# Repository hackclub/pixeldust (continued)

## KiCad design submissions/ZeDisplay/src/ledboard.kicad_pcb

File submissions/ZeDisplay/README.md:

---
name: "Burger King"
slack_id: "U07HJAL0P9Q"
tutorial: # Link to the tutorial if you used one, including the default guide
wokwi: # Link to the Wokwi project
---

# ZeDisplay

<!-- Uncomment the line below if you need a soldering iron -->
<!-- ⚠️ I would like to [reason for iron], so I would need a soldering iron. -->

A dual neopixel display with 5050 RGB LEDs and SMD-4P,2x1.8mm RGB LEDs for elegant viewing. The display is powered by a XIAO ESP32-S3 microcontroller, and uses micropython. The display is designed to be used as a decorative element in a room or as a fun project for electronics enthusiasts :)

A simplified BOM table
(pls include rough pricing of any extra components you're using)

<!-- Example: -->

| Comment           | Footprint                                      | Quantity | LCSC     | Cost   |
|-------------------|------------------------------------------------|----------|----------|--------|
| 1uF               | C_1206_3216Metric_Pad1.33x1.80mm_HandSolder    | 1        | C15008   | 0.1247$|
| 1nF               | C_0402_1005Metric_Pad0.74x0.62mm_HandSolder    | 13       | C100040  | 0.0273$|
| WS2812B           | LED_WS2812B_PLCC4_5.0x5.0mm_P3.2mm             | 80       | C22461793| 1.94$  |
| WS2812B           | XINGLIGHT XL-0807RGBC-WS2812B-S                | 140      | C41413181| 3.65$  |
| XIAO ESP32-S3     | XIAO-ESP32-S3-DIP                              | 1        |          |        |

This was more hectic to design than i imagined it to be. The power delivery was problematic, I had planned of using
USB C PD but the neotiating circuit was too complex. Not thinking about it definetly helped, I just ended up using the XIAO's 
already established power from the USB C port (implicit contract, 5V3A).

some images:

> The slikscreen has designs from the XKCD comics. <3

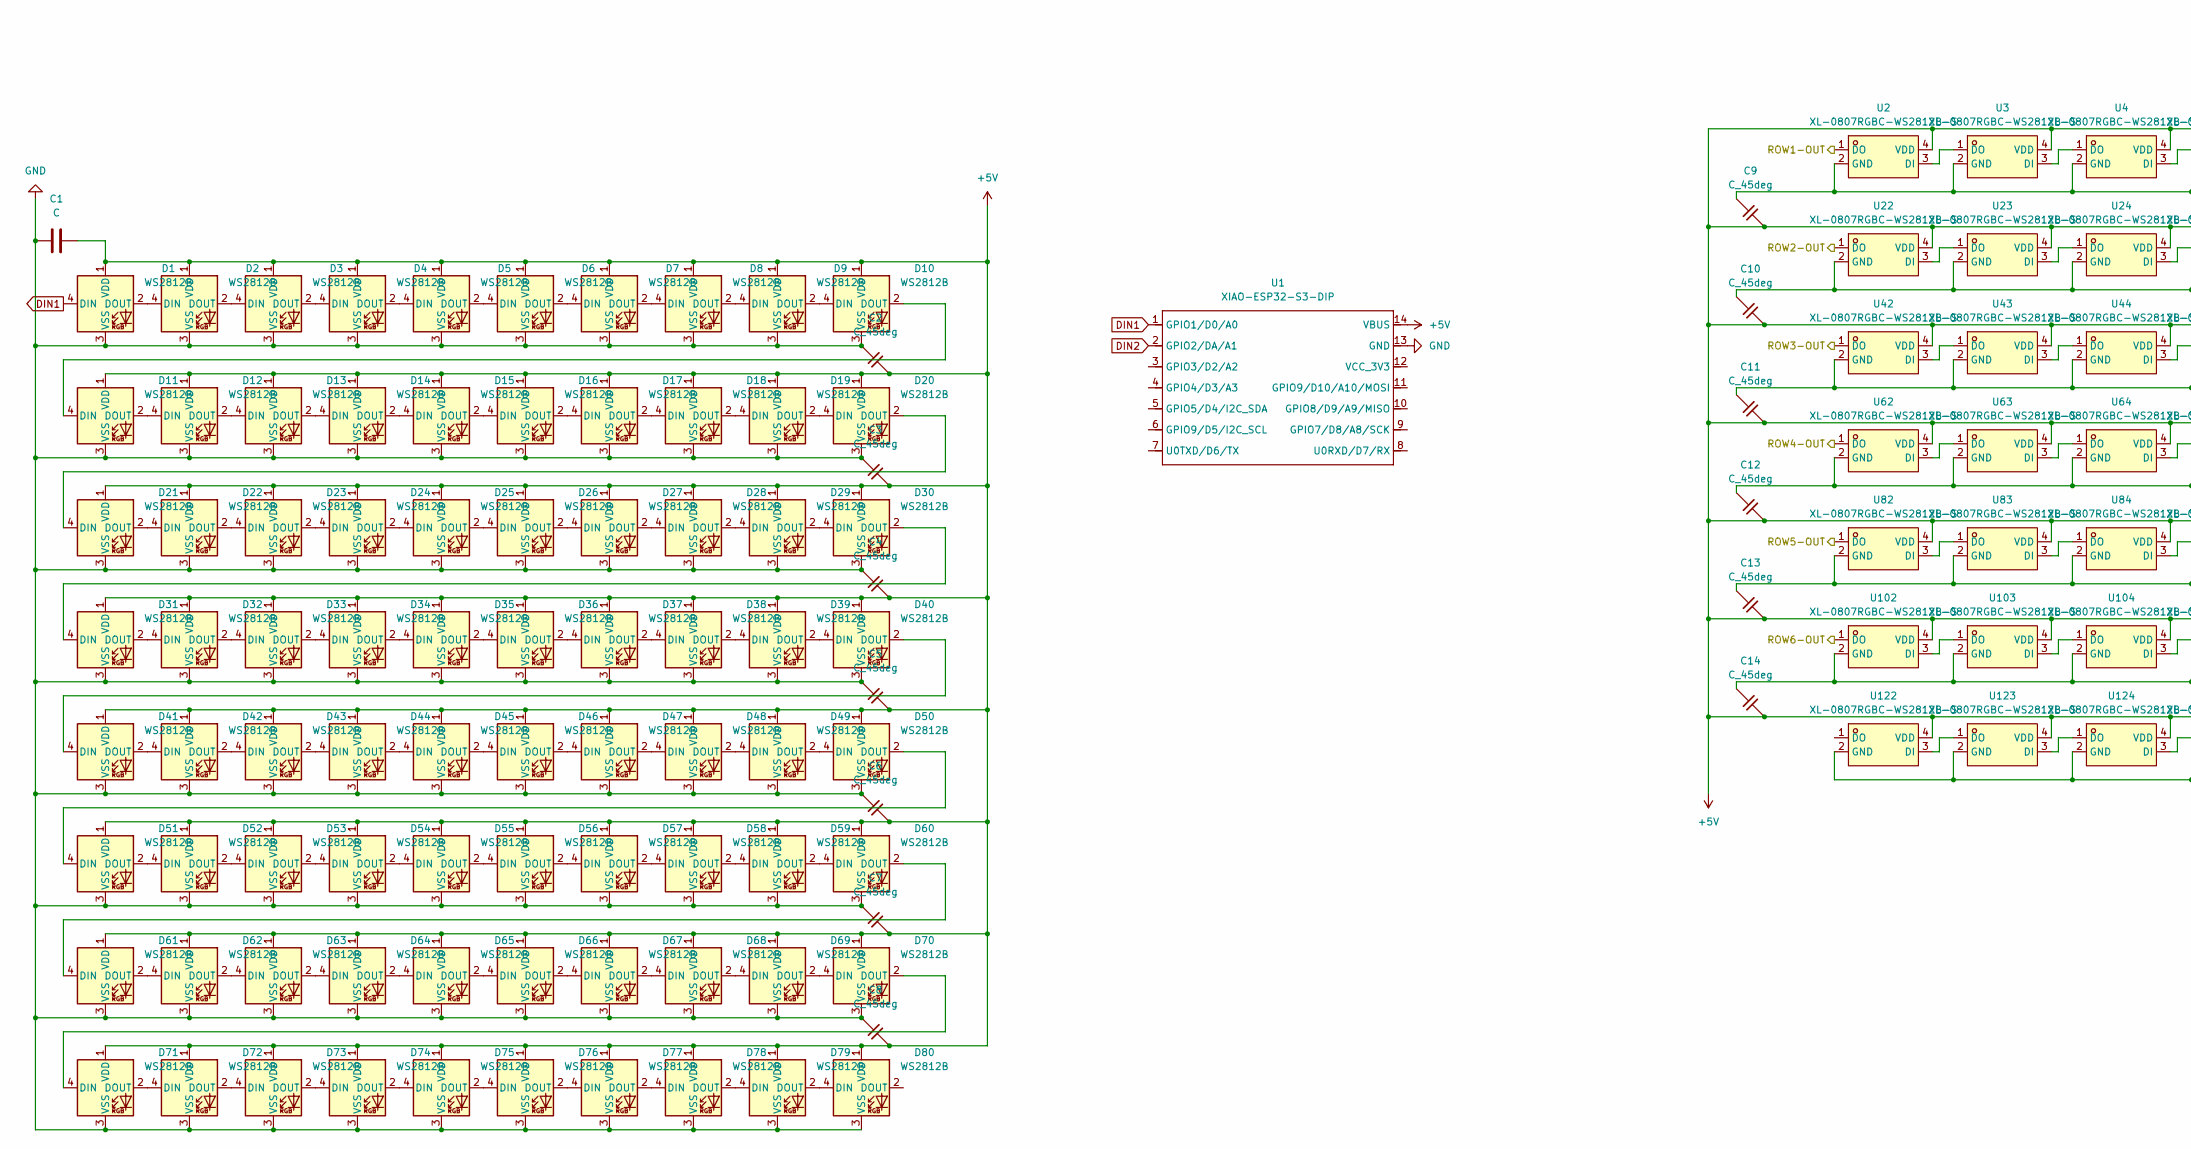
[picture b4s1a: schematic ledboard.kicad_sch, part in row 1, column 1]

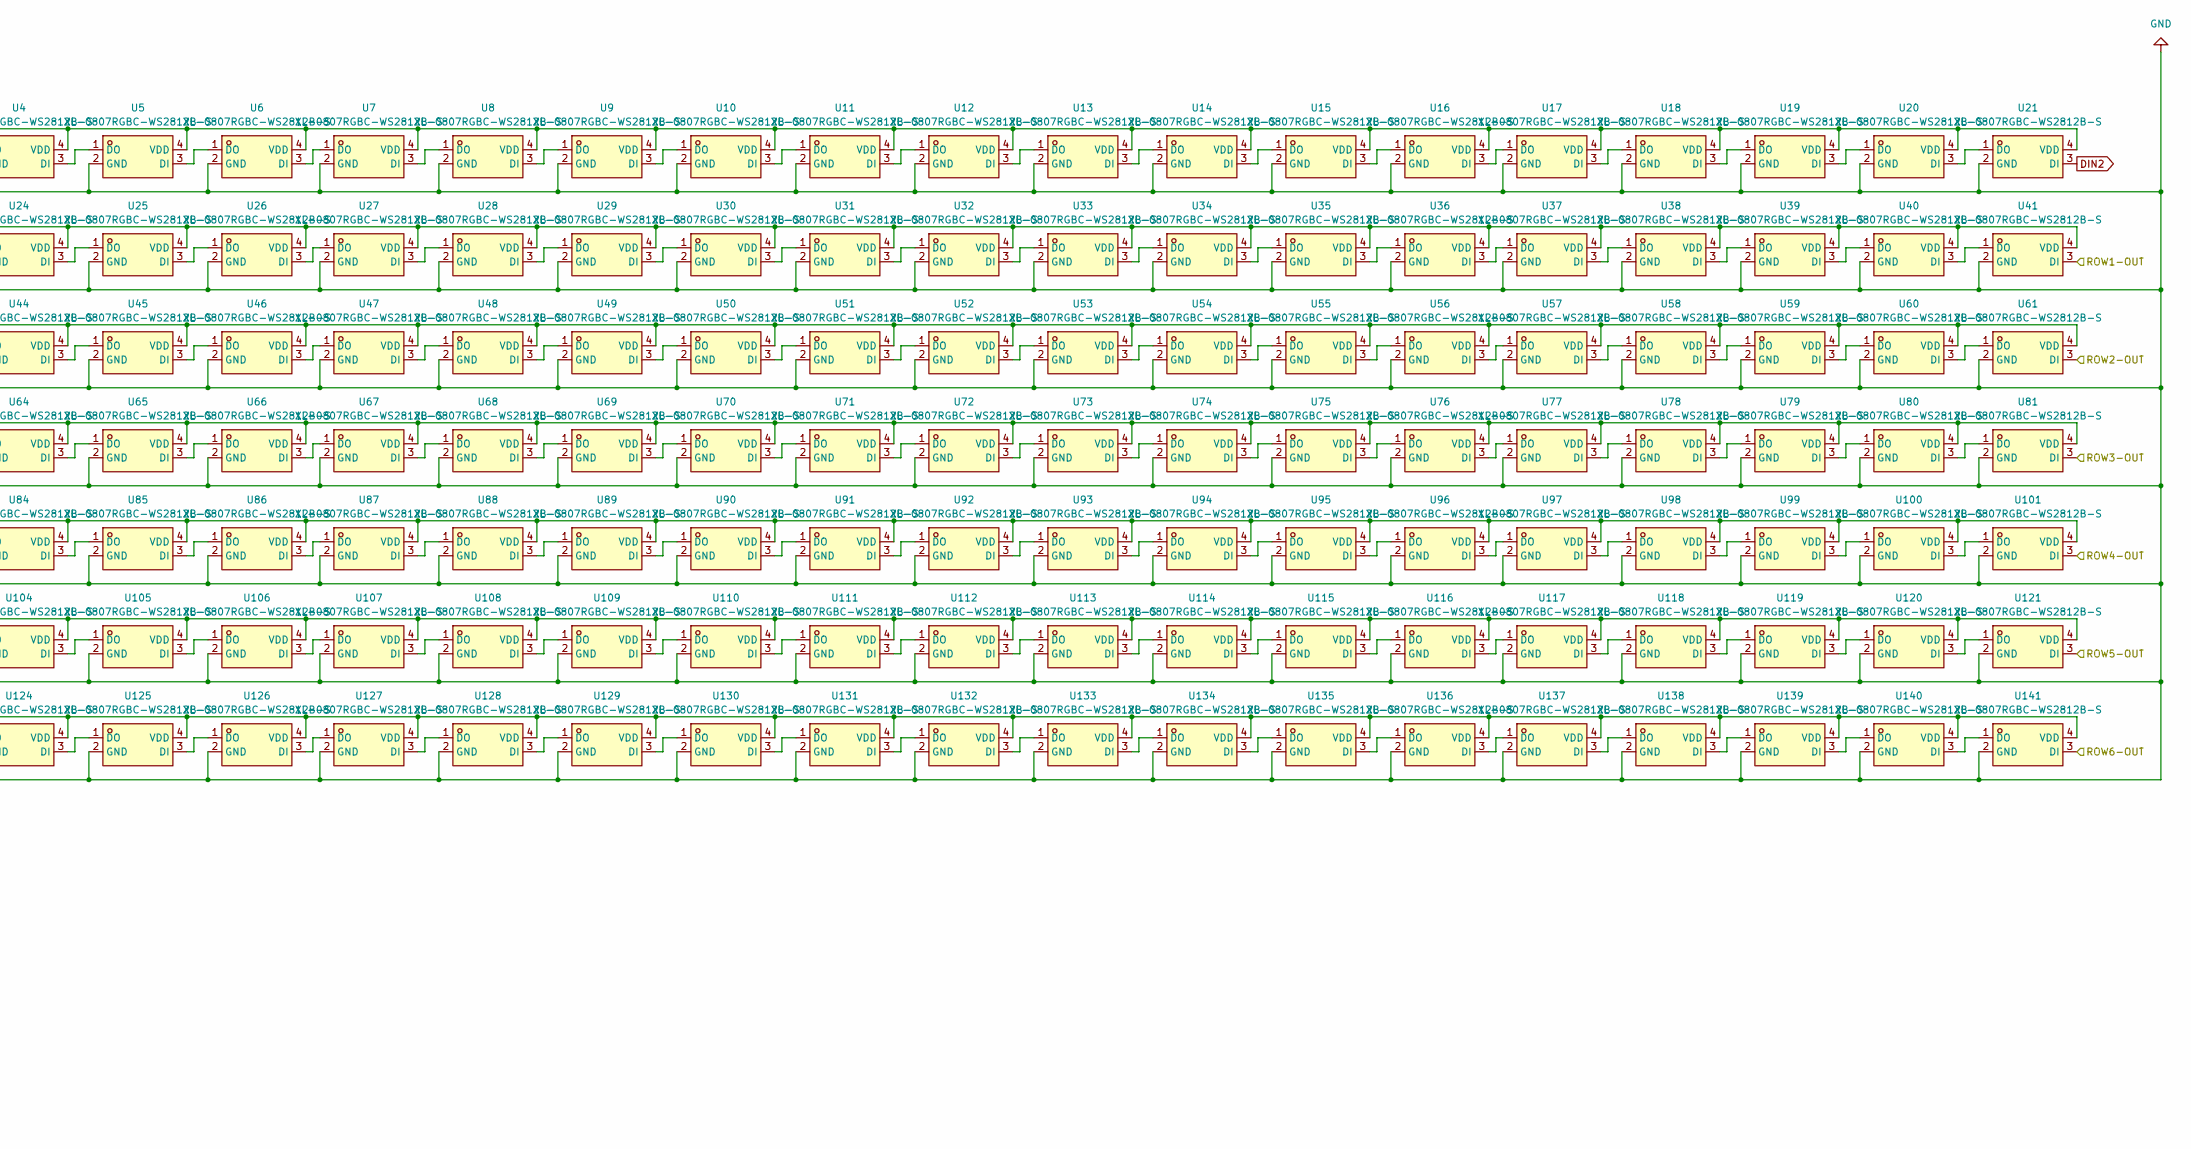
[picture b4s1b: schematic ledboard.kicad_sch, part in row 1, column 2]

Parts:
C1: C; CP_EIA-3216-18_Kemet-A_Pad1.58x1.35mm_HandSolder
C2, C3, C4, C5, C6, C7, C8, C9, C10, C11, C12, C13, C14: C_45deg; C_0603_1608Metric_Pad1.08x0.95mm_HandSolder
D1, D2, D3, D4, D5, D6, D7, D8, D9, D10, D11, D12, D13, D14, D15, D16, D17, D18, D19, D20, D21, D22, D23, D24, D25, D26, D27, D28, D29, D30, D31, D32, D33, D34, D35, D36, D37, D38, D39, D40, D41, D42, D43, D44, D45, D46, D47, D48, D49, D50, D51, D52, D53, D54, D55, D56, D57, D58, D59, D60, D61, D62, D63, D64, D65, D66, D67, D68, D69, D70, D71, D72, D73, D74, D75, D76, D77, D78, D79, D80: WS2812B; LED_WS2812B_PLCC4_5.0x5.0mm_P3.2mm
U1: XIAO-ESP32-S3-DIP; XIAO-ESP32S3-DIP
U2, U3, U4, U5, U6, U7, U8, U9, U10, U11, U12, U13, U14, U15, U16, U17, U18, U19, U20, U21, U22, U23, U24, U25, U26, U27, U28, U29, U30, U31, U32, U33, U34, U35, U36, U37, U38, U39, U40, U41, U42, U43, U44, U45, U46, U47, U48, U49, U50, U51, U52, U53, U54, U55, U56, U57, U58, U59, U60, U61, U62, U63, U64, U65, U66, U67, U68, U69, U70, U71, U72, U73, U74, U75, U76, U77, U78, U79, U80, U81, U82, U83, U84, U85, U86, U87, U88, U89, U90, U91, U92, U93, U94, U95, U96, U97, U98, U99, U100, U101, U102, U103, U104, U105, U106, U107, U108, U109, U110, U111, U112, U113, U114, U115, U116, U117, U118, U119, U120, U121, U122, U123, U124, U125, U126, U127, U128, U129, U130, U131, U132, U133, U134, U135, U136, U137, U138, U139, U140, U141: XL-0807RGBC-WS2812B-S; LED-SMD_4P-L2.0-W1.8_XL-0807RGBC-WS2812B-S; LCSC Part C41413181

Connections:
+5V: C1.1, C2.1, C3.1, C4.1, C5.1, C6.1, C7.1, C8.1, C9.1, C10.1, C11.1, C12.1, C13.1, C14.1, D1.1 (VDD), D2.1 (VDD), D3.1 (VDD), D4.1 (VDD), D5.1 (VDD), D6.1 (VDD), D7.1 (VDD), D8.1 (VDD), D9.1 (VDD), D10.1 (VDD), D11.1 (VDD), D12.1 (VDD), D13.1 (VDD), D14.1 (VDD), D15.1 (VDD), D16.1 (VDD), D17.1 (VDD), D18.1 (VDD), D19.1 (VDD), D20.1 (VDD), D21.1 (VDD), D22.1 (VDD), D23.1 (VDD), D24.1 (VDD), D25.1 (VDD), D26.1 (VDD), D27.1 (VDD), D28.1 (VDD), D29.1 (VDD), D30.1 (VDD), D31.1 (VDD), D32.1 (VDD), D33.1 (VDD), D34.1 (VDD), D35.1 (VDD), D36.1 (VDD), D37.1 (VDD), D38.1 (VDD), D39.1 (VDD), D40.1 (VDD), D41.1 (VDD), D42.1 (VDD), D43.1 (VDD), D44.1 (VDD), D45.1 (VDD), D46.1 (VDD), D47.1 (VDD), D48.1 (VDD), D49.1 (VDD), D50.1 (VDD), D51.1 (VDD), D52.1 (VDD), D53.1 (VDD), D54.1 (VDD), D55.1 (VDD), D56.1 (VDD), D57.1 (VDD), D58.1 (VDD), D59.1 (VDD), D60.1 (VDD), D61.1 (VDD), D62.1 (VDD), D63.1 (VDD), D64.1 (VDD), D65.1 (VDD), D66.1 (VDD), D67.1 (VDD), D68.1 (VDD), D69.1 (VDD), D70.1 (VDD), D71.1 (VDD), D72.1 (VDD), D73.1 (VDD), D74.1 (VDD), D75.1 (VDD), D76.1 (VDD), D77.1 (VDD), D78.1 (VDD), D79.1 (VDD), D80.1 (VDD), U1.14 (VBUS), U2.4 (VDD), U3.4 (VDD), U4.4 (VDD), U5.4 (VDD), U6.4 (VDD), U7.4 (VDD), U8.4 (VDD), U9.4 (VDD), U10.4 (VDD), U11.4 (VDD), U12.4 (VDD), U13.4 (VDD), U14.4 (VDD), U15.4 (VDD), U16.4 (VDD), U17.4 (VDD), U18.4 (VDD), U19.4 (VDD), U20.4 (VDD), U21.4 (VDD), U22.4 (VDD), U23.4 (VDD), U24.4 (VDD), U25.4 (VDD), U26.4 (VDD), U27.4 (VDD), U28.4 (VDD), U29.4 (VDD), U30.4 (VDD), U31.4 (VDD), U32.4 (VDD), U33.4 (VDD), U34.4 (VDD), U35.4 (VDD), U36.4 (VDD), U37.4 (VDD), U38.4 (VDD), U39.4 (VDD), U40.4 (VDD), U41.4 (VDD), U42.4 (VDD), U43.4 (VDD), U44.4 (VDD), U45.4 (VDD), U46.4 (VDD), U47.4 (VDD), U48.4 (VDD), U49.4 (VDD), U50.4 (VDD), U51.4 (VDD), U52.4 (VDD), U53.4 (VDD), U54.4 (VDD), U55.4 (VDD), U56.4 (VDD), U57.4 (VDD), U58.4 (VDD), U59.4 (VDD), U60.4 (VDD), U61.4 (VDD), U62.4 (VDD), U63.4 (VDD), U64.4 (VDD), U65.4 (VDD), U66.4 (VDD), U67.4 (VDD), U68.4 (VDD), U69.4 (VDD), U70.4 (VDD), U71.4 (VDD), U72.4 (VDD), U73.4 (VDD), U74.4 (VDD), U75.4 (VDD), U76.4 (VDD), U77.4 (VDD), U78.4 (VDD), U79.4 (VDD), U80.4 (VDD), U81.4 (VDD), U82.4 (VDD), U83.4 (VDD), U84.4 (VDD), U85.4 (VDD), U86.4 (VDD), U87.4 (VDD), U88.4 (VDD), U89.4 (VDD), U90.4 (VDD), U91.4 (VDD), U92.4 (VDD), U93.4 (VDD), U94.4 (VDD), U95.4 (VDD), U96.4 (VDD), U97.4 (VDD), U98.4 (VDD), U99.4 (VDD), U100.4 (VDD), U101.4 (VDD), U102.4 (VDD), U103.4 (VDD), U104.4 (VDD), U105.4 (VDD), U106.4 (VDD), U107.4 (VDD), U108.4 (VDD), U109.4 (VDD), U110.4 (VDD), U111.4 (VDD), U112.4 (VDD), U113.4 (VDD), U114.4 (VDD), U115.4 (VDD), U116.4 (VDD), U117.4 (VDD), U118.4 (VDD), U119.4 (VDD), U120.4 (VDD), U121.4 (VDD), U122.4 (VDD), U123.4 (VDD), U124.4 (VDD), U125.4 (VDD), U126.4 (VDD), U127.4 (VDD), U128.4 (VDD), U129.4 (VDD), U130.4 (VDD), U131.4 (VDD), U132.4 (VDD), U133.4 (VDD), U134.4 (VDD), U135.4 (VDD), U136.4 (VDD), U137.4 (VDD), U138.4 (VDD), U139.4 (VDD), U140.4 (VDD), U141.4 (VDD)
/ROW1-OUT: U2.1 (DO), U41.3 (DI)
/ROW2-OUT: U22.1 (DO), U61.3 (DI)
/ROW3-OUT: U42.1 (DO), U81.3 (DI)
/ROW4-OUT: U62.1 (DO), U101.3 (DI)
/ROW5-OUT: U82.1 (DO), U121.3 (DI)
/ROW6-OUT: U102.1 (DO), U141.3 (DI)
DIN1: D1.4 (DIN), U1.1 (GPIO1/D0/A0)
DIN2: U1.2 (GPIO2/DA/A1), U21.3 (DI)
GND: C1.2, C2.2, C3.2, C4.2, C5.2, C6.2, C7.2, C8.2, C9.2, C10.2, C11.2, C12.2, C13.2, C14.2, D1.3 (VSS), D2.3 (VSS), D3.3 (VSS), D4.3 (VSS), D5.3 (VSS), D6.3 (VSS), D7.3 (VSS), D8.3 (VSS), D9.3 (VSS), D10.3 (VSS), D11.3 (VSS), D12.3 (VSS), D13.3 (VSS), D14.3 (VSS), D15.3 (VSS), D16.3 (VSS), D17.3 (VSS), D18.3 (VSS), D19.3 (VSS), D20.3 (VSS), D21.3 (VSS), D22.3 (VSS), D23.3 (VSS), D24.3 (VSS), D25.3 (VSS), D26.3 (VSS), D27.3 (VSS), D28.3 (VSS), D29.3 (VSS), D30.3 (VSS), D31.3 (VSS), D32.3 (VSS), D33.3 (VSS), D34.3 (VSS), D35.3 (VSS), D36.3 (VSS), D37.3 (VSS), D38.3 (VSS), D39.3 (VSS), D40.3 (VSS), D41.3 (VSS), D42.3 (VSS), D43.3 (VSS), D44.3 (VSS), D45.3 (VSS), D46.3 (VSS), D47.3 (VSS), D48.3 (VSS), D49.3 (VSS), D50.3 (VSS), D51.3 (VSS), D52.3 (VSS), D53.3 (VSS), D54.3 (VSS), D55.3 (VSS), D56.3 (VSS), D57.3 (VSS), D58.3 (VSS), D59.3 (VSS), D60.3 (VSS), D61.3 (VSS), D62.3 (VSS), D63.3 (VSS), D64.3 (VSS), D65.3 (VSS), D66.3 (VSS), D67.3 (VSS), D68.3 (VSS), D69.3 (VSS), D70.3 (VSS), D71.3 (VSS), D72.3 (VSS), D73.3 (VSS), D74.3 (VSS), D75.3 (VSS), D76.3 (VSS), D77.3 (VSS), D78.3 (VSS), D79.3 (VSS), D80.3 (VSS), U1.13 (GND), U2.2 (GND), U3.2 (GND), U4.2 (GND), U5.2 (GND), U6.2 (GND), U7.2 (GND), U8.2 (GND), U9.2 (GND), U10.2 (GND), U11.2 (GND), U12.2 (GND), U13.2 (GND), U14.2 (GND), U15.2 (GND), U16.2 (GND), U17.2 (GND), U18.2 (GND), U19.2 (GND), U20.2 (GND), U21.2 (GND), U22.2 (GND), U23.2 (GND), U24.2 (GND), U25.2 (GND), U26.2 (GND), U27.2 (GND), U28.2 (GND), U29.2 (GND), U30.2 (GND), U31.2 (GND), U32.2 (GND), U33.2 (GND), U34.2 (GND), U35.2 (GND), U36.2 (GND), U37.2 (GND), U38.2 (GND), U39.2 (GND), U40.2 (GND), U41.2 (GND), U42.2 (GND), U43.2 (GND), U44.2 (GND), U45.2 (GND), U46.2 (GND), U47.2 (GND), U48.2 (GND), U49.2 (GND), U50.2 (GND), U51.2 (GND), U52.2 (GND), U53.2 (GND), U54.2 (GND), U55.2 (GND), U56.2 (GND), U57.2 (GND), U58.2 (GND), U59.2 (GND), U60.2 (GND), U61.2 (GND), U62.2 (GND), U63.2 (GND), U64.2 (GND), U65.2 (GND), U66.2 (GND), U67.2 (GND), U68.2 (GND), U69.2 (GND), U70.2 (GND), U71.2 (GND), U72.2 (GND), U73.2 (GND), U74.2 (GND), U75.2 (GND), U76.2 (GND), U77.2 (GND), U78.2 (GND), U79.2 (GND), U80.2 (GND), U81.2 (GND), U82.2 (GND), U83.2 (GND), U84.2 (GND), U85.2 (GND), U86.2 (GND), U87.2 (GND), U88.2 (GND), U89.2 (GND), U90.2 (GND), U91.2 (GND), U92.2 (GND), U93.2 (GND), U94.2 (GND), U95.2 (GND), U96.2 (GND), U97.2 (GND), U98.2 (GND), U99.2 (GND), U100.2 (GND), U101.2 (GND), U102.2 (GND), U103.2 (GND), U104.2 (GND), U105.2 (GND), U106.2 (GND), U107.2 (GND), U108.2 (GND), U109.2 (GND), U110.2 (GND), U111.2 (GND), U112.2 (GND), U113.2 (GND), U114.2 (GND), U115.2 (GND), U116.2 (GND), U117.2 (GND), U118.2 (GND), U119.2 (GND), U120.2 (GND), U121.2 (GND), U122.2 (GND), U123.2 (GND), U124.2 (GND), U125.2 (GND), U126.2 (GND), U127.2 (GND), U128.2 (GND), U129.2 (GND), U130.2 (GND), U131.2 (GND), U132.2 (GND), U133.2 (GND), U134.2 (GND), U135.2 (GND), U136.2 (GND), U137.2 (GND), U138.2 (GND), U139.2 (GND), U140.2 (GND), U141.2 (GND)
unnamed: D1.2 (DOUT), D2.4 (DIN)
unnamed: D2.2 (DOUT), D3.4 (DIN)
unnamed: D3.2 (DOUT), D4.4 (DIN)
unnamed: D4.2 (DOUT), D5.4 (DIN)
unnamed: D5.2 (DOUT), D6.4 (DIN)
unnamed: D6.2 (DOUT), D7.4 (DIN)
unnamed: D7.2 (DOUT), D8.4 (DIN)
unnamed: D8.2 (DOUT), D9.4 (DIN)
unnamed: D9.2 (DOUT), D10.4 (DIN)
unnamed: D10.2 (DOUT), D11.4 (DIN)
unnamed: D11.2 (DOUT), D12.4 (DIN)
unnamed: D12.2 (DOUT), D13.4 (DIN)
unnamed: D13.2 (DOUT), D14.4 (DIN)
unnamed: D14.2 (DOUT), D15.4 (DIN)
unnamed: D15.2 (DOUT), D16.4 (DIN)
unnamed: D16.2 (DOUT), D17.4 (DIN)
unnamed: D17.2 (DOUT), D18.4 (DIN)
unnamed: D18.2 (DOUT), D19.4 (DIN)
unnamed: D19.2 (DOUT), D20.4 (DIN)
unnamed: D20.2 (DOUT), D21.4 (DIN)
unnamed: D21.2 (DOUT), D22.4 (DIN)
unnamed: D22.2 (DOUT), D23.4 (DIN)
unnamed: D23.2 (DOUT), D24.4 (DIN)
unnamed: D24.2 (DOUT), D25.4 (DIN)
unnamed: D25.2 (DOUT), D26.4 (DIN)
unnamed: D26.2 (DOUT), D27.4 (DIN)
unnamed: D27.2 (DOUT), D28.4 (DIN)
unnamed: D28.2 (DOUT), D29.4 (DIN)
unnamed: D29.2 (DOUT), D30.4 (DIN)
unnamed: D30.2 (DOUT), D31.4 (DIN)
unnamed: D31.2 (DOUT), D32.4 (DIN)
unnamed: D32.2 (DOUT), D33.4 (DIN)
unnamed: D33.2 (DOUT), D34.4 (DIN)
unnamed: D34.2 (DOUT), D35.4 (DIN)
unnamed: D35.2 (DOUT), D36.4 (DIN)
unnamed: D36.2 (DOUT), D37.4 (DIN)
unnamed: D37.2 (DOUT), D38.4 (DIN)
unnamed: D38.2 (DOUT), D39.4 (DIN)
unnamed: D39.2 (DOUT), D40.4 (DIN)
unnamed: D40.2 (DOUT), D41.4 (DIN)
unnamed: D41.2 (DOUT), D42.4 (DIN)
unnamed: D42.2 (DOUT), D43.4 (DIN)
unnamed: D43.2 (DOUT), D44.4 (DIN)
unnamed: D44.2 (DOUT), D45.4 (DIN)
unnamed: D45.2 (DOUT), D46.4 (DIN)
unnamed: D46.2 (DOUT), D47.4 (DIN)
unnamed: D47.2 (DOUT), D48.4 (DIN)
unnamed: D48.2 (DOUT), D49.4 (DIN)
unnamed: D49.2 (DOUT), D50.4 (DIN)
unnamed: D50.2 (DOUT), D51.4 (DIN)
unnamed: D51.2 (DOUT), D52.4 (DIN)
unnamed: D52.2 (DOUT), D53.4 (DIN)
unnamed: D53.2 (DOUT), D54.4 (DIN)
unnamed: D54.2 (DOUT), D55.4 (DIN)
unnamed: D55.2 (DOUT), D56.4 (DIN)
unnamed: D56.2 (DOUT), D57.4 (DIN)
unnamed: D57.2 (DOUT), D58.4 (DIN)
unnamed: D58.2 (DOUT), D59.4 (DIN)
unnamed: D59.2 (DOUT), D60.4 (DIN)
unnamed: D60.2 (DOUT), D61.4 (DIN)
unnamed: D61.2 (DOUT), D62.4 (DIN)
unnamed: D62.2 (DOUT), D63.4 (DIN)
unnamed: D63.2 (DOUT), D64.4 (DIN)
unnamed: D64.2 (DOUT), D65.4 (DIN)
unnamed: D65.2 (DOUT), D66.4 (DIN)
unnamed: D66.2 (DOUT), D67.4 (DIN)
unnamed: D67.2 (DOUT), D68.4 (DIN)
unnamed: D68.2 (DOUT), D69.4 (DIN)
unnamed: D69.2 (DOUT), D70.4 (DIN)
unnamed: D70.2 (DOUT), D71.4 (DIN)
unnamed: D71.2 (DOUT), D72.4 (DIN)
unnamed: D72.2 (DOUT), D73.4 (DIN)
unnamed: D73.2 (DOUT), D74.4 (DIN)
unnamed: D74.2 (DOUT), D75.4 (DIN)
unnamed: D75.2 (DOUT), D76.4 (DIN)
unnamed: D76.2 (DOUT), D77.4 (DIN)
unnamed: D77.2 (DOUT), D78.4 (DIN)
unnamed: D78.2 (DOUT), D79.4 (DIN)
unnamed: D79.2 (DOUT), D80.4 (DIN)
unnamed: U2.3 (DI), U3.1 (DO)
unnamed: U3.3 (DI), U4.1 (DO)
unnamed: U4.3 (DI), U5.1 (DO)
unnamed: U5.3 (DI), U6.1 (DO)
unnamed: U6.3 (DI), U7.1 (DO)
unnamed: U7.3 (DI), U8.1 (DO)
unnamed: U8.3 (DI), U9.1 (DO)
unnamed: U10.3 (DI), U11.1 (DO)
unnamed: U9.3 (DI), U10.1 (DO)
unnamed: U11.3 (DI), U12.1 (DO)
unnamed: U12.3 (DI), U13.1 (DO)
unnamed: U13.3 (DI), U14.1 (DO)
unnamed: U14.3 (DI), U15.1 (DO)
unnamed: U15.3 (DI), U16.1 (DO)
unnamed: U16.3 (DI), U17.1 (DO)
unnamed: U17.3 (DI), U18.1 (DO)
unnamed: U18.3 (DI), U19.1 (DO)
unnamed: U19.3 (DI), U20.1 (DO)
unnamed: U20.3 (DI), U21.1 (DO)
unnamed: U22.3 (DI), U23.1 (DO)
unnamed: U23.3 (DI), U24.1 (DO)
unnamed: U24.3 (DI), U25.1 (DO)
unnamed: U25.3 (DI), U26.1 (DO)
unnamed: U26.3 (DI), U27.1 (DO)
unnamed: U27.3 (DI), U28.1 (DO)
unnamed: U28.3 (DI), U29.1 (DO)
unnamed: U29.3 (DI), U30.1 (DO)
unnamed: U30.3 (DI), U31.1 (DO)
unnamed: U31.3 (DI), U32.1 (DO)
unnamed: U32.3 (DI), U33.1 (DO)
unnamed: U33.3 (DI), U34.1 (DO)
unnamed: U34.3 (DI), U35.1 (DO)
unnamed: U35.3 (DI), U36.1 (DO)
unnamed: U36.3 (DI), U37.1 (DO)
unnamed: U37.3 (DI), U38.1 (DO)
unnamed: U38.3 (DI), U39.1 (DO)
unnamed: U39.3 (DI), U40.1 (DO)
unnamed: U40.3 (DI), U41.1 (DO)
unnamed: U42.3 (DI), U43.1 (DO)
unnamed: U43.3 (DI), U44.1 (DO)
unnamed: U44.3 (DI), U45.1 (DO)
unnamed: U45.3 (DI), U46.1 (DO)
unnamed: U46.3 (DI), U47.1 (DO)
unnamed: U47.3 (DI), U48.1 (DO)
unnamed: U48.3 (DI), U49.1 (DO)
unnamed: U49.3 (DI), U50.1 (DO)
unnamed: U50.3 (DI), U51.1 (DO)
unnamed: U51.3 (DI), U52.1 (DO)
unnamed: U52.3 (DI), U53.1 (DO)
unnamed: U53.3 (DI), U54.1 (DO)
unnamed: U54.3 (DI), U55.1 (DO)
unnamed: U55.3 (DI), U56.1 (DO)
unnamed: U56.3 (DI), U57.1 (DO)
unnamed: U57.3 (DI), U58.1 (DO)
unnamed: U58.3 (DI), U59.1 (DO)
unnamed: U59.3 (DI), U60.1 (DO)
unnamed: U60.3 (DI), U61.1 (DO)
unnamed: U62.3 (DI), U63.1 (DO)
unnamed: U63.3 (DI), U64.1 (DO)
unnamed: U64.3 (DI), U65.1 (DO)
unnamed: U65.3 (DI), U66.1 (DO)
unnamed: U66.3 (DI), U67.1 (DO)
unnamed: U67.3 (DI), U68.1 (DO)
unnamed: U68.3 (DI), U69.1 (DO)
unnamed: U69.3 (DI), U70.1 (DO)
unnamed: U70.3 (DI), U71.1 (DO)
unnamed: U71.3 (DI), U72.1 (DO)
unnamed: U72.3 (DI), U73.1 (DO)
unnamed: U73.3 (DI), U74.1 (DO)
unnamed: U74.3 (DI), U75.1 (DO)
unnamed: U75.3 (DI), U76.1 (DO)
unnamed: U76.3 (DI), U77.1 (DO)
unnamed: U77.3 (DI), U78.1 (DO)
unnamed: U78.3 (DI), U79.1 (DO)
unnamed: U79.3 (DI), U80.1 (DO)
unnamed: U80.3 (DI), U81.1 (DO)
unnamed: U82.3 (DI), U83.1 (DO)
unnamed: U83.3 (DI), U84.1 (DO)
unnamed: U84.3 (DI), U85.1 (DO)
unnamed: U85.3 (DI), U86.1 (DO)
unnamed: U86.3 (DI), U87.1 (DO)
unnamed: U87.3 (DI), U88.1 (DO)
unnamed: U88.3 (DI), U89.1 (DO)
unnamed: U89.3 (DI), U90.1 (DO)
unnamed: U90.3 (DI), U91.1 (DO)
unnamed: U91.3 (DI), U92.1 (DO)
unnamed: U92.3 (DI), U93.1 (DO)
unnamed: U93.3 (DI), U94.1 (DO)
unnamed: U94.3 (DI), U95.1 (DO)
unnamed: U95.3 (DI), U96.1 (DO)
unnamed: U96.3 (DI), U97.1 (DO)
unnamed: U97.3 (DI), U98.1 (DO)
unnamed: U98.3 (DI), U99.1 (DO)
unnamed: U100.3 (DI), U101.1 (DO)
unnamed: U99.3 (DI), U100.1 (DO)
unnamed: U102.3 (DI), U103.1 (DO)
unnamed: U103.3 (DI), U104.1 (DO)
unnamed: U104.3 (DI), U105.1 (DO)
unnamed: U105.3 (DI), U106.1 (DO)
unnamed: U106.3 (DI), U107.1 (DO)
unnamed: U107.3 (DI), U108.1 (DO)
unnamed: U108.3 (DI), U109.1 (DO)
unnamed: U109.3 (DI), U110.1 (DO)
unnamed: U110.3 (DI), U111.1 (DO)
unnamed: U111.3 (DI), U112.1 (DO)
unnamed: U112.3 (DI), U113.1 (DO)
unnamed: U113.3 (DI), U114.1 (DO)
unnamed: U114.3 (DI), U115.1 (DO)
unnamed: U115.3 (DI), U116.1 (DO)
unnamed: U116.3 (DI), U117.1 (DO)
unnamed: U117.3 (DI), U118.1 (DO)
unnamed: U118.3 (DI), U119.1 (DO)
unnamed: U119.3 (DI), U120.1 (DO)
unnamed: U120.3 (DI), U121.1 (DO)
unnamed: U122.3 (DI), U123.1 (DO)
unnamed: U123.3 (DI), U124.1 (DO)
unnamed: U124.3 (DI), U125.1 (DO)
unnamed: U125.3 (DI), U126.1 (DO)
unnamed: U126.3 (DI), U127.1 (DO)
unnamed: U127.3 (DI), U128.1 (DO)
unnamed: U128.3 (DI), U129.1 (DO)
unnamed: U129.3 (DI), U130.1 (DO)
unnamed: U130.3 (DI), U131.1 (DO)
unnamed: U131.3 (DI), U132.1 (DO)
unnamed: U132.3 (DI), U133.1 (DO)
unnamed: U133.3 (DI), U134.1 (DO)
unnamed: U134.3 (DI), U135.1 (DO)
unnamed: U135.3 (DI), U136.1 (DO)
unnamed: U136.3 (DI), U137.1 (DO)
unnamed: U137.3 (DI), U138.1 (DO)
unnamed: U138.3 (DI), U139.1 (DO)
unnamed: U139.3 (DI), U140.1 (DO)
unnamed: U140.3 (DI), U141.1 (DO)

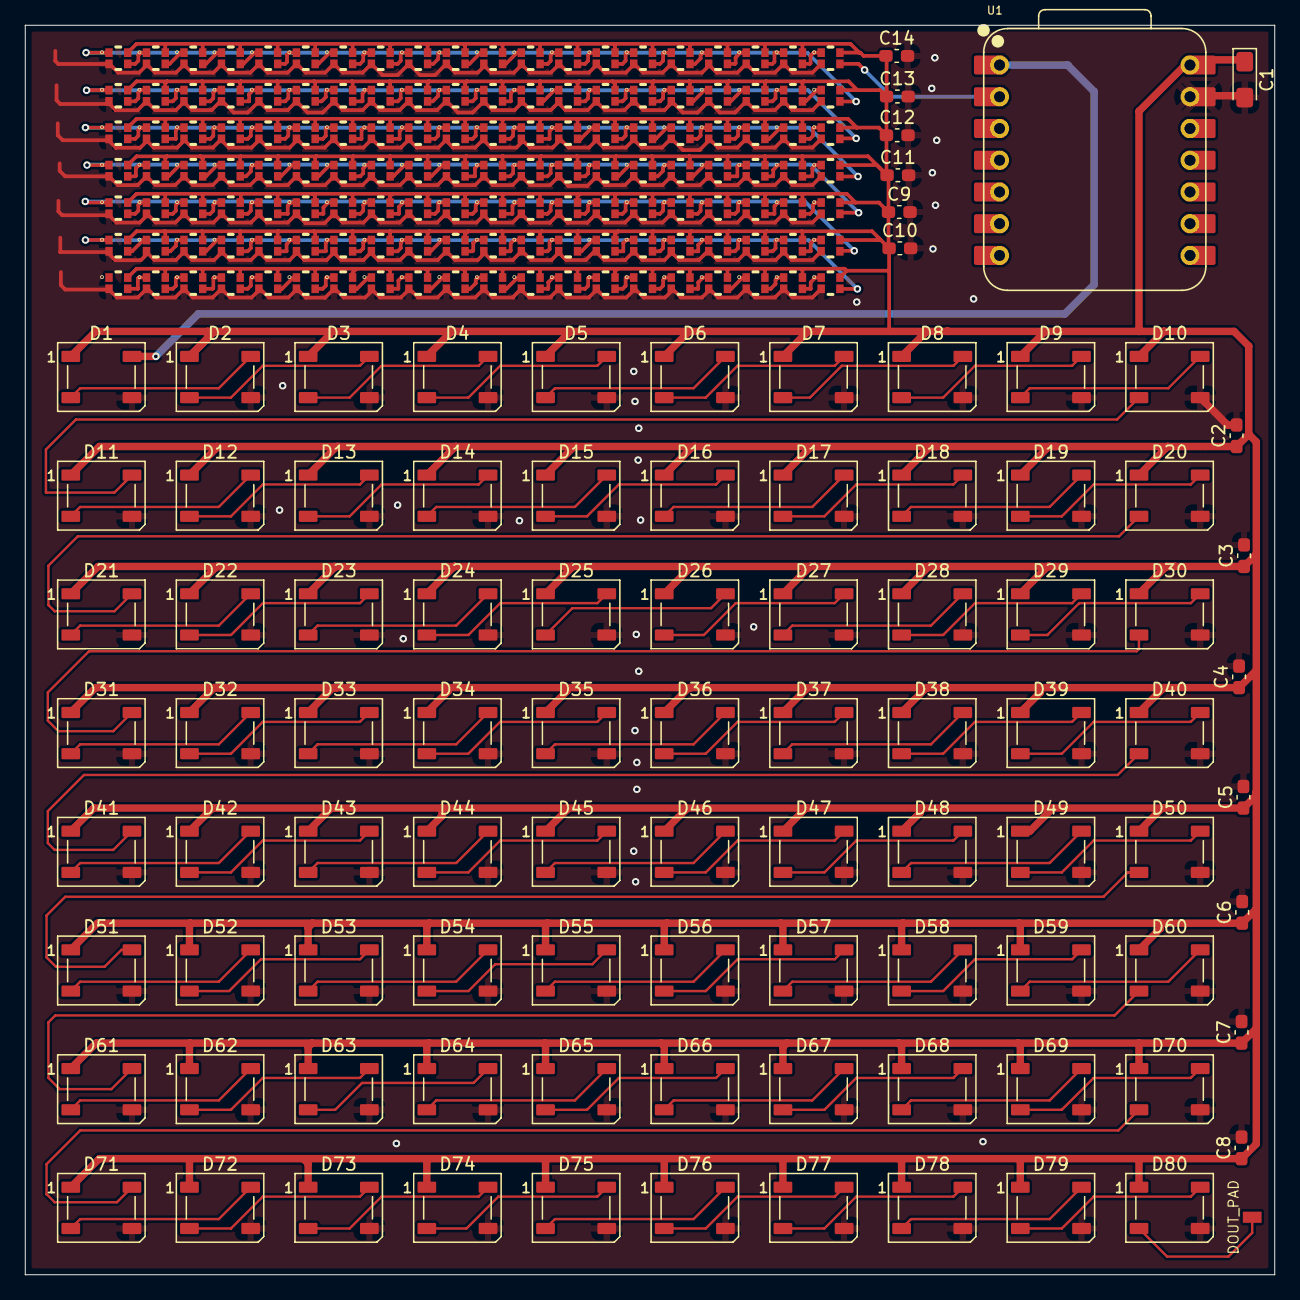
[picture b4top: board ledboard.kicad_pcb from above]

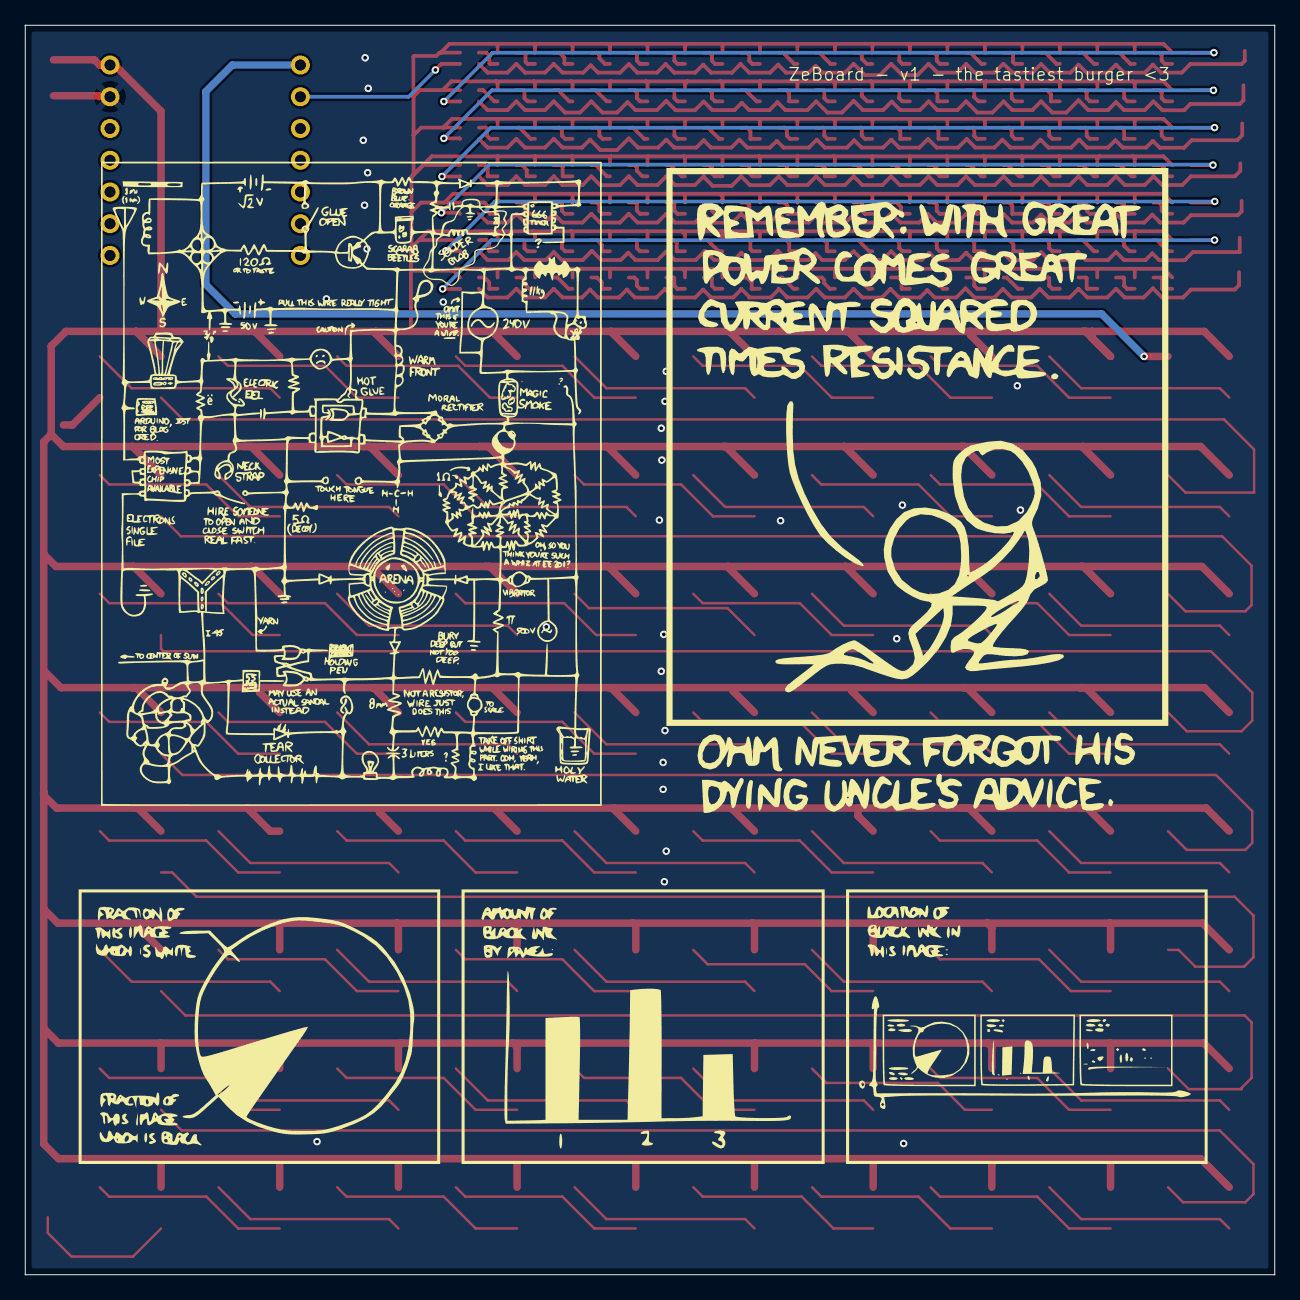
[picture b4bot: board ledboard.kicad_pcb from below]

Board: 2 copper layers, 100.0 x 100.0 mm, 239 parts (3 on the bottom side), 222 nets.

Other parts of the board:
 : LOGO
 #2,  #3: LOGO
DOUT_PAD: (no value)

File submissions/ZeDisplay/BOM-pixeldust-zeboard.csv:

"Reference","Qty","Value","DNP","Exclude from BOM","Exclude from Board","Footprint","Datasheet"
"C1","1","1uf","","","","Capacitor_Tantalum_SMD:CP_EIA-3216-18_Kemet-A_Pad1.58x1.35mm_HandSolder","~"
"C2,C3,C4,C5,C6,C7,C8,C9,C10,C11,C12,C13,C14","13","1nf","","","","Capacitor_SMD:C_0603_1608Metric_Pad1.08x0.95mm_HandSolder","~"
"D1,D2,D3,D4,D5,D6,D7,D8,D9,D10,D11,D12,D13,D14,D15,D16,D17,D18,D19,D20,D21,D22,D23,D24,D25,D26,D27,D28,D29,D30,D31,D32,D33,D34,D35,D36,D37,D38,D39,D40,D41,D42,D43,D44,D45,D46,D47,D48,D49,D50,D51,D52,D53,D54,D55,D56,D57,D58,D59,D60,D61,D62,D63,D64,D65,D66,D67,D68,D69,D70,D71,D72,D73,D74,D75,D76,D77,D78,D79,D80","80","WS2812B","","","","LED_SMD:LED_WS2812B_PLCC4_5.0x5.0mm_P3.2mm",""
"U1","1","XIAO-ESP32-S3-DIP","","","","xiao:XIAO-ESP32S3-DIP",""
"U2,U3,U4,U5,U6,U7,U8,U9,U10,U11,U12,U13,U14,U15,U16,U17,U18,U19,U20,U21,U22,U23,U24,U25,U26,U27,U28,U29,U30,U31,U32,U33,U34,U35,U36,U37,U38,U39,U40,U41,U42,U43,U44,U45,U46,U47,U48,U49,U50,U51,U52,U53,U54,U55,U56,U57,U58,U59,U60,U61,U62,U63,U64,U65,U66,U67,U68,U69,U70,U71,U72,U73,U74,U75,U76,U77,U78,U79,U80,U81,U82,U83,U84,U85,U86,U87,U88,U89,U90,U91,U92,U93,U94,U95,U96,U97,U98,U99,U100,U101,U102,U103,U104,U105,U106,U107,U108,U109,U110,U111,U112,U113,U114,U115,U116,U117,U118,U119,U120,U121,U122,U123,U124,U125,U126,U127,U128,U129,U130,U131,U132,U133,U134,U135,U136,U137,U138,U139,U140,U141","140","XL-0807RGBC-WS2812B-S","","","","XINGLIGHT XL-0807RGBC-WS2812B-S:LED-SMD_4P-L2.0-W1.8_XL-0807RGBC-WS2812B-S",""

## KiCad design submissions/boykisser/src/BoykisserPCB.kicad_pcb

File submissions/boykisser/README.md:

---
name: "Meng Ray Lai"
slack_id: "U07FPDRVCD8"
github_handle: "@YeetTheAnson"
tutorial: "None"
wokwi: "https://wokwi.com/projects/428126154408852481"
---

# Boykisser keychain

Wokwi link: [https://wokwi.com/projects/428126154408852481](https://wokwi.com/projects/428126154408852481)

This is mauzymice's boykisser on a PCB keychain with addressable RGB leds. This is just for fun and has no actual use (apart from attracting furries, of course) and I plan to add bluetooth support when I have more time. The current code is extremely simple, there's 4 colour profiles that gets cycled when the boot button on the Seeed Xiao esp32-s3 is pressed. To fill in the gap and diffuse the LED behind the "blush", I plan to add either hot glue or silicone. I might add a small boost converter and a lithium battery charging module as well to power the keychain wirelessly.

Critical specifications in JLCPCB:
1. PCB Color must be Black
2. "Remove Mark" option must be selected under High-spec Options > Mark on PCB

Note:
1. Yes, some of the SK6812Mini-EA pads will be cut off and this should be fine
2. I plan to solder this PCB myself, is it possible to get the PCB shipped directly to me? (From JLCPCB)

Bill Of Material

| Comment           | Footprint                                      | Quantity | LCSC     | Cost   |
|-------------------|------------------------------------------------|----------|----------|--------|
| SK6812-5050       | SK6812    | 6        | -     |  -   |
| SK6812MINI-EA     | SK6812MINI-E   | 2        | -     |  -   |
| XIAO ESP32-S3     | XIAO-RP2040-DIP                                | 1        | -     |  -   |

I need a hotplate and some solder paste if possible :3

Initially, I wanted to take a shortcut by finding an image online and using KiCad's image converter to create the edge cuts. However, I quickly realized that this method wouldn't work as it gave broken and jagged edge cuts. Then, I decided to design the edge cuts and rule zone manually by tracing over the original image (real). It took about 2 hours to design the PCB without any components.

Once the base PCB outline was complete, I spent the next hour picking and placing the components. After that, I've spent another hour and a half to writing a simple Arduino sketch that cycles through four different color profiles with each press of the boot button. To validate the design, I wired everything up in the Wokwi simulator. Initially, the circuit didn’t work as the LEDs to the same pin as the USB line. It took me a longer time that I'd like to admit to find the problem. With that done, I quickly fixed the code and updated the PCB routing.

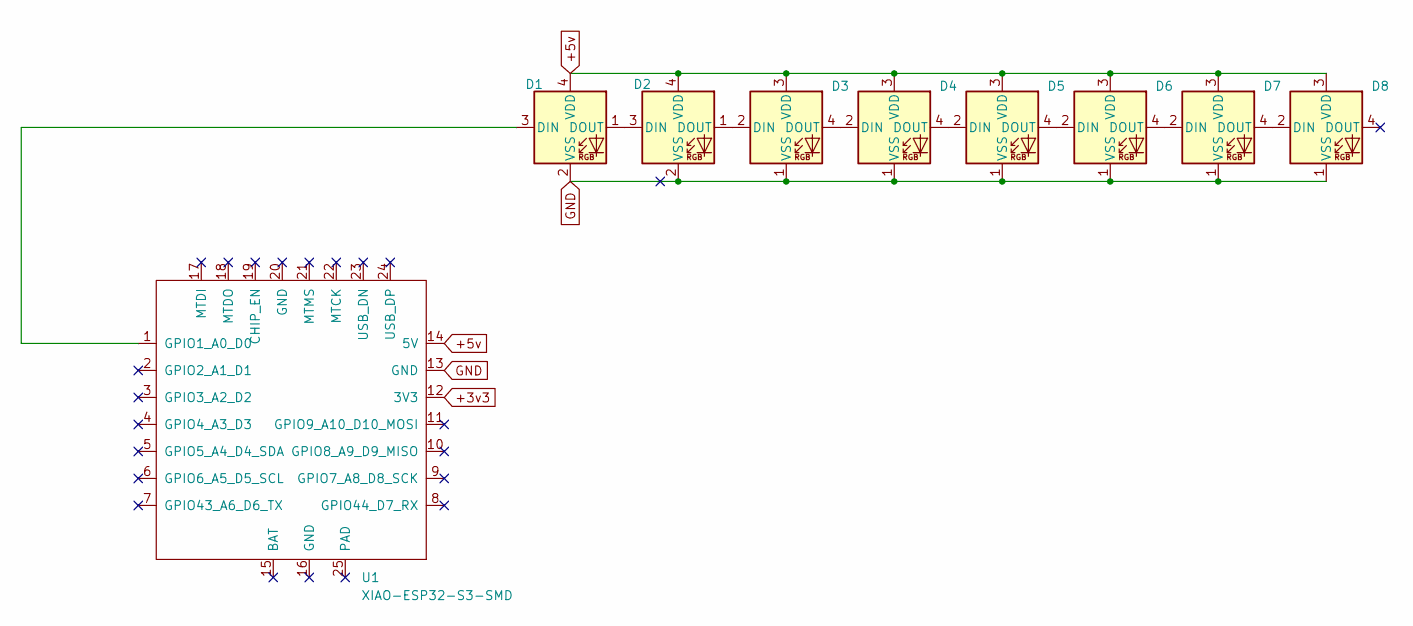
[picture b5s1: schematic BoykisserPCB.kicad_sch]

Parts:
D1, D2: SK6812MINI; SK6812MINI-E
D3, D4, D5, D6, D7, D8: SK6812; LED_SK6812_PLCC4_5.0x5.0mm_P3.2mm
U1: XIAO-ESP32-S3-SMD; XIAO-ESP32S3-SMD

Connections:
+3v3: U1.12 (3V3)
+5v: D1.4 (VDD), D2.4 (VDD), D3.3 (VDD), D4.3 (VDD), D5.3 (VDD), D6.3 (VDD), D7.3 (VDD), D8.3 (VDD), U1.14 (5V)
GND: D1.2 (VSS), D2.2 (VSS), D3.1 (VSS), D4.1 (VSS), D5.1 (VSS), D6.1 (VSS), D7.1 (VSS), D8.1 (VSS), U1.13 (GND)
unnamed: D1.3 (DIN), U1.1 (GPIO1_A0_D0)
unnamed: D1.1 (DOUT), D2.3 (DIN)
unnamed: D2.1 (DOUT), D3.2 (DIN)
unnamed: D3.4 (DOUT), D4.2 (DIN)
unnamed: D4.4 (DOUT), D5.2 (DIN)
unnamed: D5.4 (DOUT), D6.2 (DIN)
unnamed: D6.4 (DOUT), D7.2 (DIN)
unnamed: D7.4 (DOUT), D8.2 (DIN)

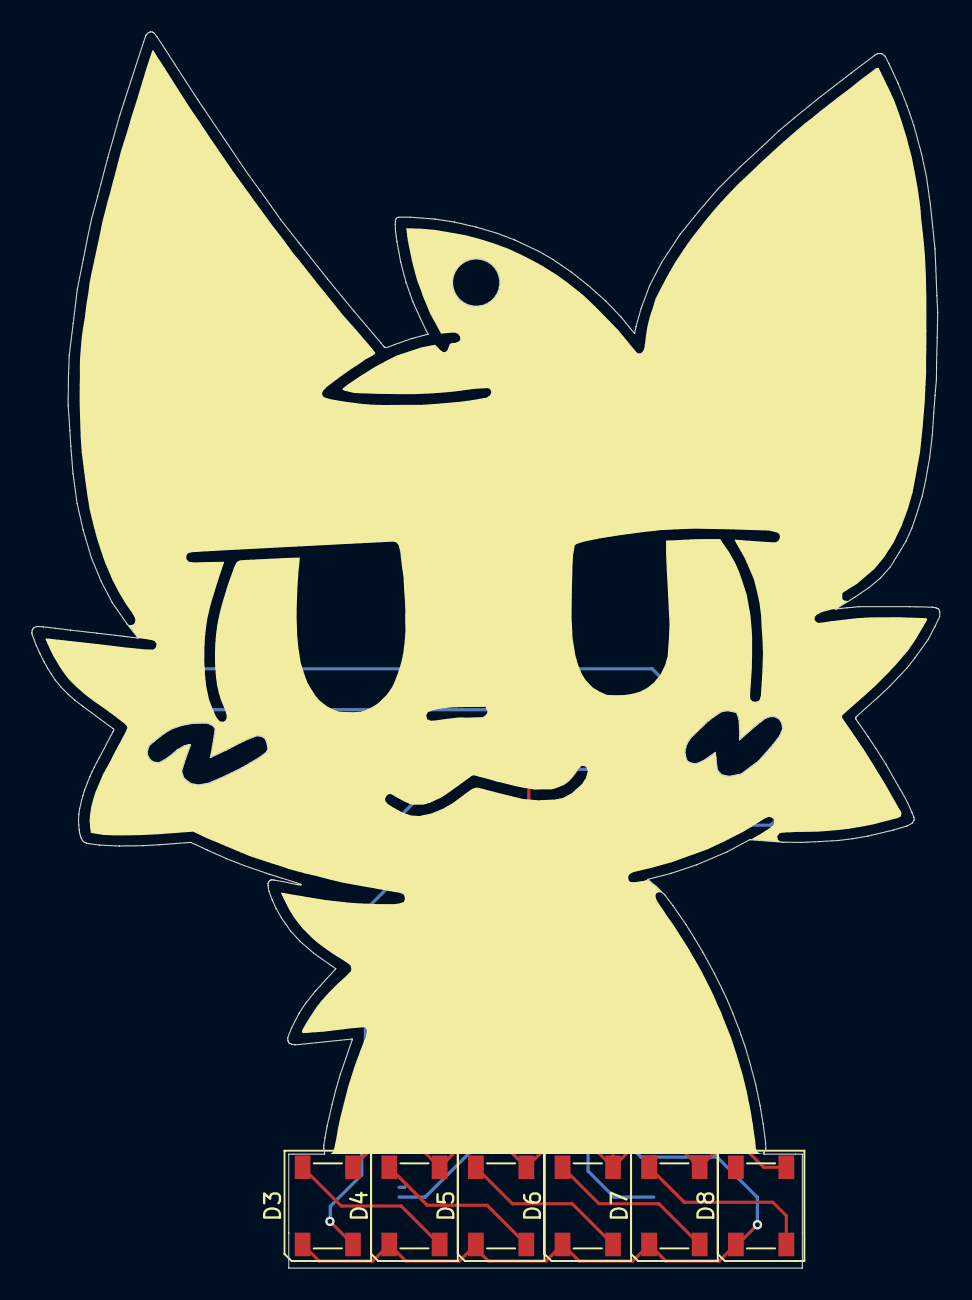
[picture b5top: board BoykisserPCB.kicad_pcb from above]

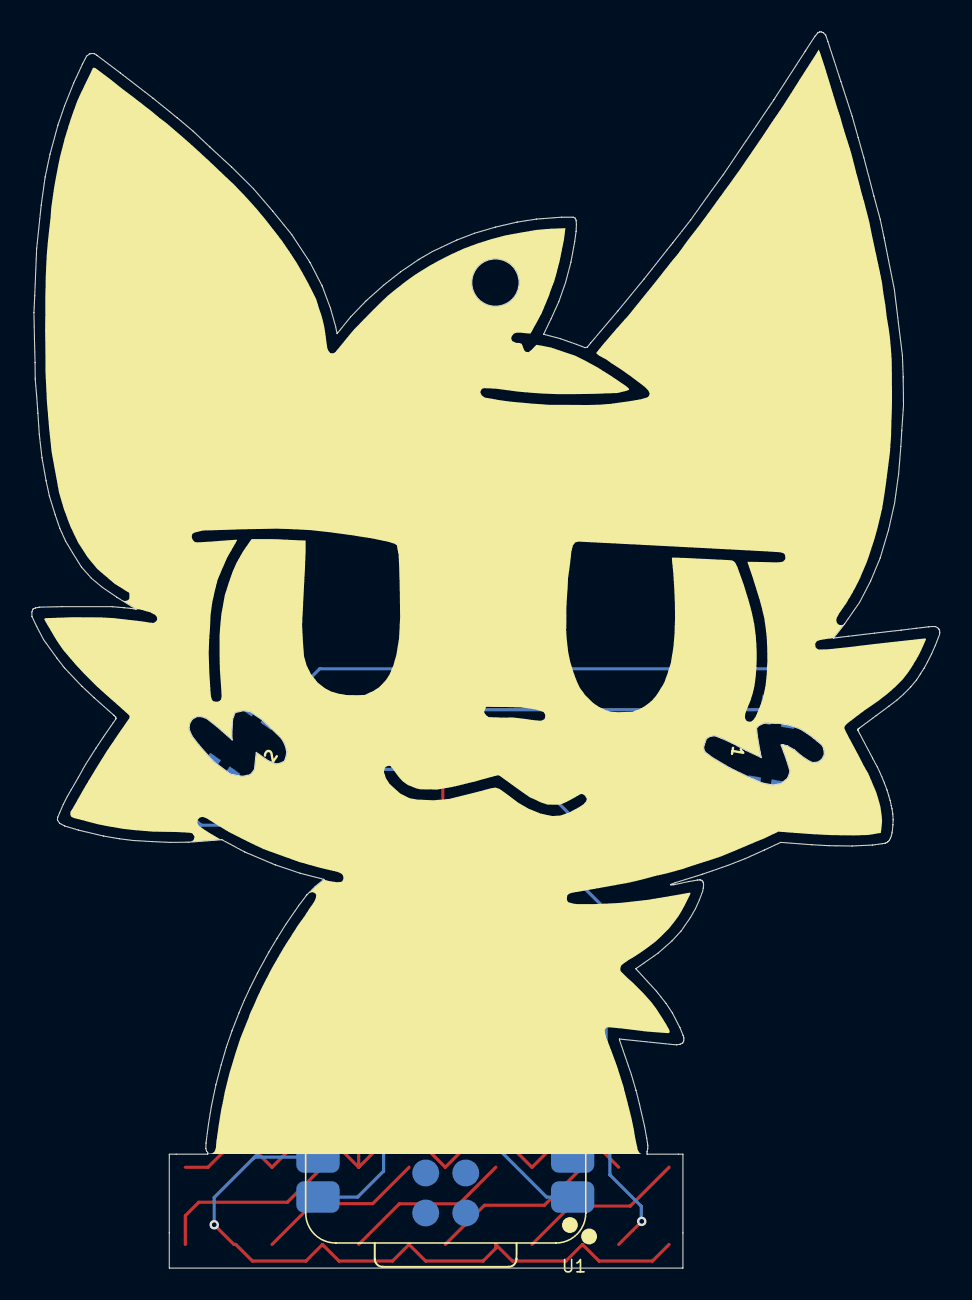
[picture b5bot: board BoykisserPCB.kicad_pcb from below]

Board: 2 copper layers, 57.6 x 78.5 mm, 9 parts (3 on the bottom side), 10 nets.
